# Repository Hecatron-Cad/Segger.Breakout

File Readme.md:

# Segger Breakout

This is a simple kicad design for a breakout board for the JLink Segger.

  * https://www.segger.com/products/debug-probes/j-link/models/j-link-edu/

It also has pads for connecting an ESP32 ProS3, or a Rpi Pico 2040
To clone use
```sh
git clone --recurse-submodules https://github.com/Hecatron-Cad/Segger.Breakout.git
```

## VCC Pins

I've added a jumper for the VCC input to VTref on the segger.
some pages suggest not to connect it when the device is powered over usb, but I think this is incorrect.
Still I added a jumper just in case anyway

  * https://www.visualmicro.com/page/ESP32-Debugging.aspx

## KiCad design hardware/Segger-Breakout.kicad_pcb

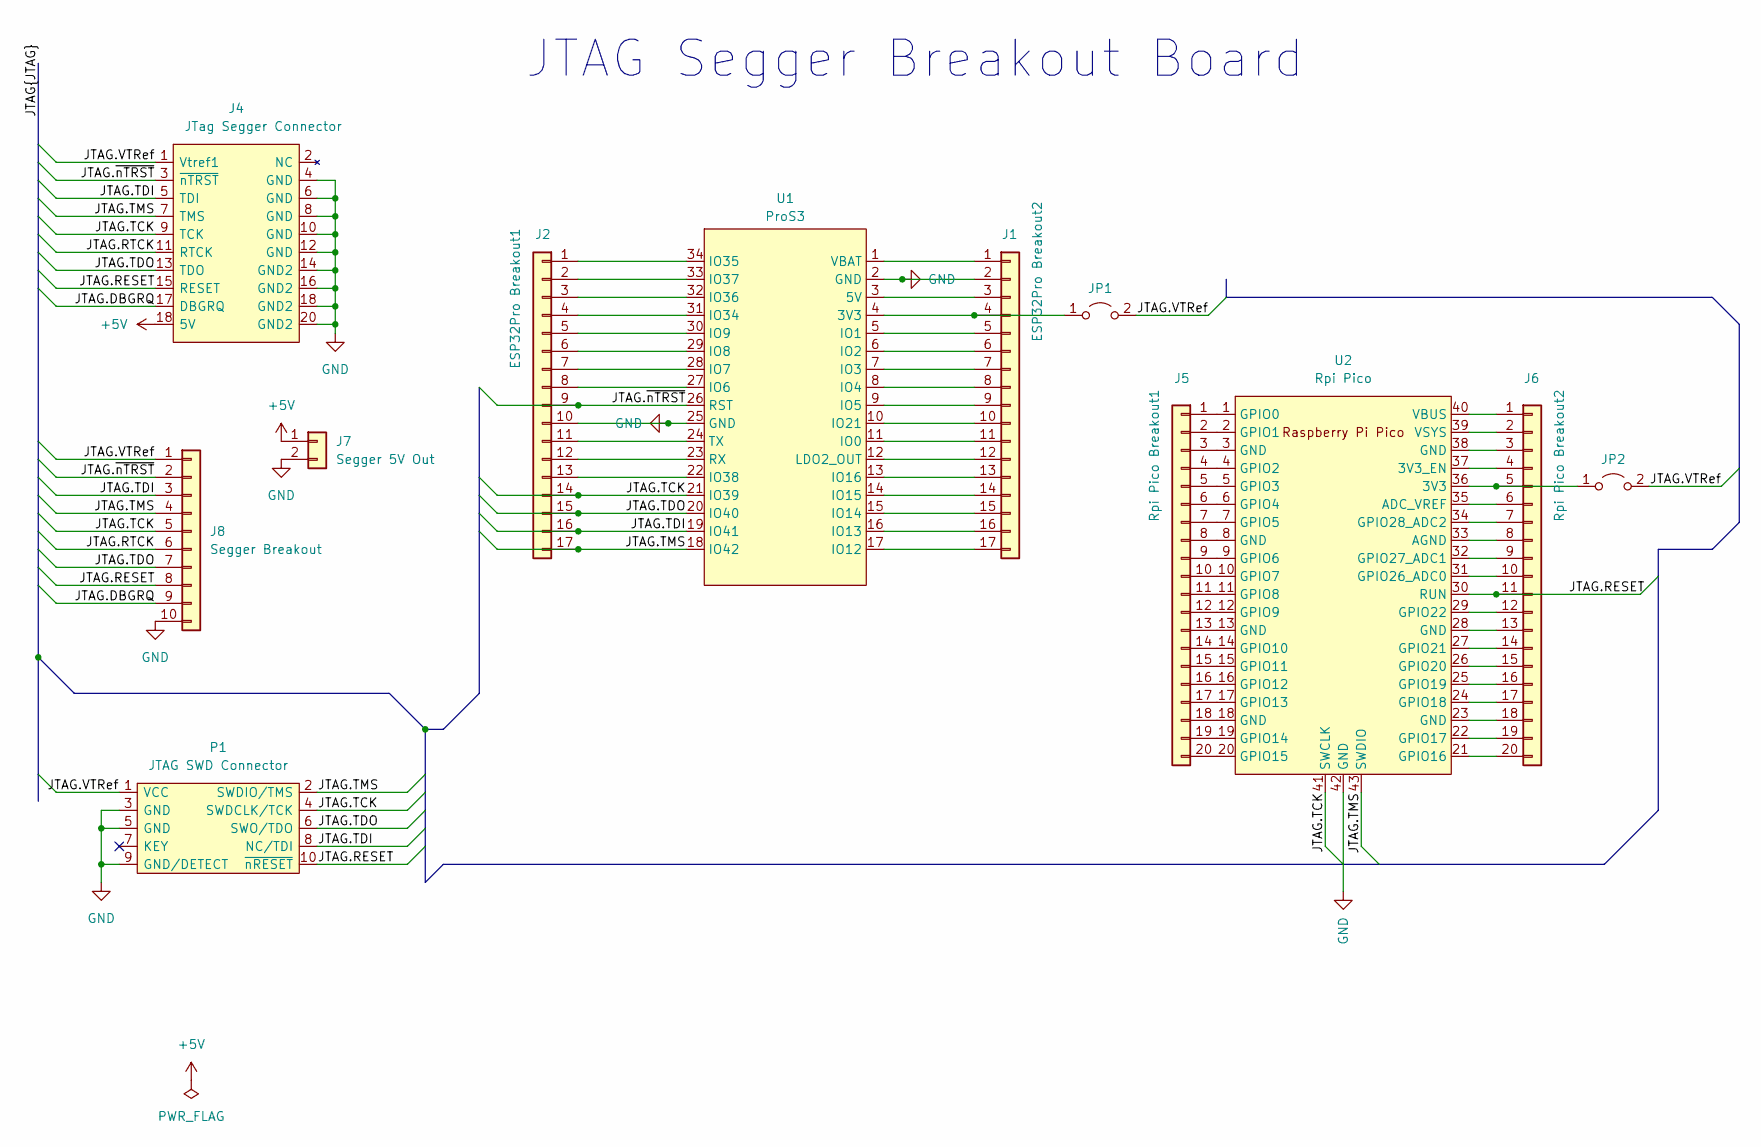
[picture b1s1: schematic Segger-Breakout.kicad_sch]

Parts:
J1: ESP32Pro Breakout2; PinHeader_1x17_P2.54mm_Vertical
J2: ESP32Pro Breakout1; PinHeader_1x17_P2.54mm_Vertical
J4: JTag Segger Connector; IDC-Header_2x10_P2.54mm_Vertical
J5: Rpi Pico Breakout1; PinHeader_1x20_P2.54mm_Vertical
J6: Rpi Pico Breakout2; PinHeader_1x20_P2.54mm_Vertical
J7: Segger 5V Out; PinHeader_1x02_P2.54mm_Vertical
J8: Segger Breakout; PinHeader_1x10_P2.54mm_Vertical
JP1, JP2: VTref Segger Input; PinSocket_1x02_P2.54mm_Vertical
P1: JTAG SWD Connector; ARM_10_PIN
U1: ProS3; ProS3_TH
U2: Rpi Pico; RPi_PicoW_SMD_TH

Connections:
/JTAG.DBGRQ: J4.17 (DBGRQ), J8.9
/JTAG.RESET: J4.15 (RESET), J6.11, J8.8, P1.10 (~nRESET), U2.30 (RUN)
/JTAG.RTCK: J4.11 (RTCK), J8.6
/JTAG.TCK: J2.14, J4.9 (TCK), J8.5, P1.4 (SWDCLK/TCK), U1.21 (IO39), U2.41 (SWCLK)
/JTAG.TDI: J2.16, J4.5 (TDI), J8.3, P1.8 (NC/TDI), U1.19 (IO41)
/JTAG.TDO: J2.15, J4.13 (TDO), J8.7, P1.6 (SWO/TDO), U1.20 (IO40)
/JTAG.TMS: J2.17, J4.7 (TMS), J8.4, P1.2 (SWDIO/TMS), U1.18 (IO42), U2.43 (SWDIO)
/JTAG.VTRef: J4.1 (Vtref1), J8.1, JP1.2 (B), JP2.2 (B), P1.1 (VCC)
/JTAG.~nTRST: J2.9, J4.3 (~nTRST), J8.2, U1.26 (RST)
unnamed: J1.1, U1.1 (VBAT)
unnamed: J1.3, U1.3 (5V)
unnamed: J1.4, JP1.1 (A), U1.4 (3V3)
unnamed: J1.5, U1.5 (IO1)
unnamed: J1.6, U1.6 (IO2)
unnamed: J1.7, U1.7 (IO3)
unnamed: J1.8, U1.8 (IO4)
unnamed: J1.9, U1.9 (IO5)
unnamed: J1.10, U1.10 (IO21)
unnamed: J1.11, U1.11 (IO0)
unnamed: J1.12, U1.12 (LDO2_OUT)
unnamed: J1.13, U1.13 (IO16)
unnamed: J1.14, U1.14 (IO15)
unnamed: J1.15, U1.15 (IO14)
unnamed: J1.16, U1.16 (IO13)
unnamed: J1.17, U1.17 (IO12)
unnamed: J2.1, U1.34 (IO35)
unnamed: J2.2, U1.33 (IO37)
unnamed: J2.3, U1.32 (IO36)
unnamed: J2.4, U1.31 (IO34)
unnamed: J2.5, U1.30 (IO9)
unnamed: J2.6, U1.29 (IO8)
unnamed: J2.7, U1.28 (IO7)
unnamed: J2.8, U1.27 (IO6)
unnamed: J2.11, U1.24 (TX)
unnamed: J2.12, U1.23 (RX)
unnamed: J2.13, U1.22 (IO38)
unnamed: J5.1, U2.1 (GPIO0)
unnamed: J5.2, U2.2 (GPIO1)
unnamed: J5.3, U2.3 (GND)
unnamed: J5.4, U2.4 (GPIO2)
unnamed: J5.5, U2.5 (GPIO3)
unnamed: J5.6, U2.6 (GPIO4)
unnamed: J5.7, U2.7 (GPIO5)
unnamed: J5.8, U2.8 (GND)
unnamed: J5.9, U2.9 (GPIO6)
unnamed: J5.10, U2.10 (GPIO7)
unnamed: J5.11, U2.11 (GPIO8)
unnamed: J5.12, U2.12 (GPIO9)
unnamed: J5.13, U2.13 (GND)
unnamed: J5.14, U2.14 (GPIO10)
unnamed: J5.15, U2.15 (GPIO11)
unnamed: J5.16, U2.16 (GPIO12)
unnamed: J5.17, U2.17 (GPIO13)
unnamed: J5.18, U2.18 (GND)
unnamed: J5.19, U2.19 (GPIO14)
unnamed: J5.20, U2.20 (GPIO15)
unnamed: J6.1, U2.40 (VBUS)
unnamed: J6.2, U2.39 (VSYS)
unnamed: J6.3, U2.38 (GND)
unnamed: J6.4, U2.37 (3V3_EN)
unnamed: J6.5, JP2.1 (A), U2.36 (3V3)
unnamed: J6.6, U2.35 (ADC_VREF)
unnamed: J6.7, U2.34 (GPIO28_ADC2)
unnamed: J6.8, U2.33 (AGND)
unnamed: J6.9, U2.32 (GPIO27_ADC1)
unnamed: J6.10, U2.31 (GPIO26_ADC0)
unnamed: J6.12, U2.29 (GPIO22)
unnamed: J6.13, U2.28 (GND)
unnamed: J6.14, U2.27 (GPIO21)
unnamed: J6.15, U2.26 (GPIO20)
unnamed: J6.16, U2.25 (GPIO19)
unnamed: J6.17, U2.24 (GPIO18)
unnamed: J6.18, U2.23 (GND)
unnamed: J6.19, U2.22 (GPIO17)
unnamed: J6.20, U2.21 (GPIO16)

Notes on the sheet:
JTAG Segger Breakout Board

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
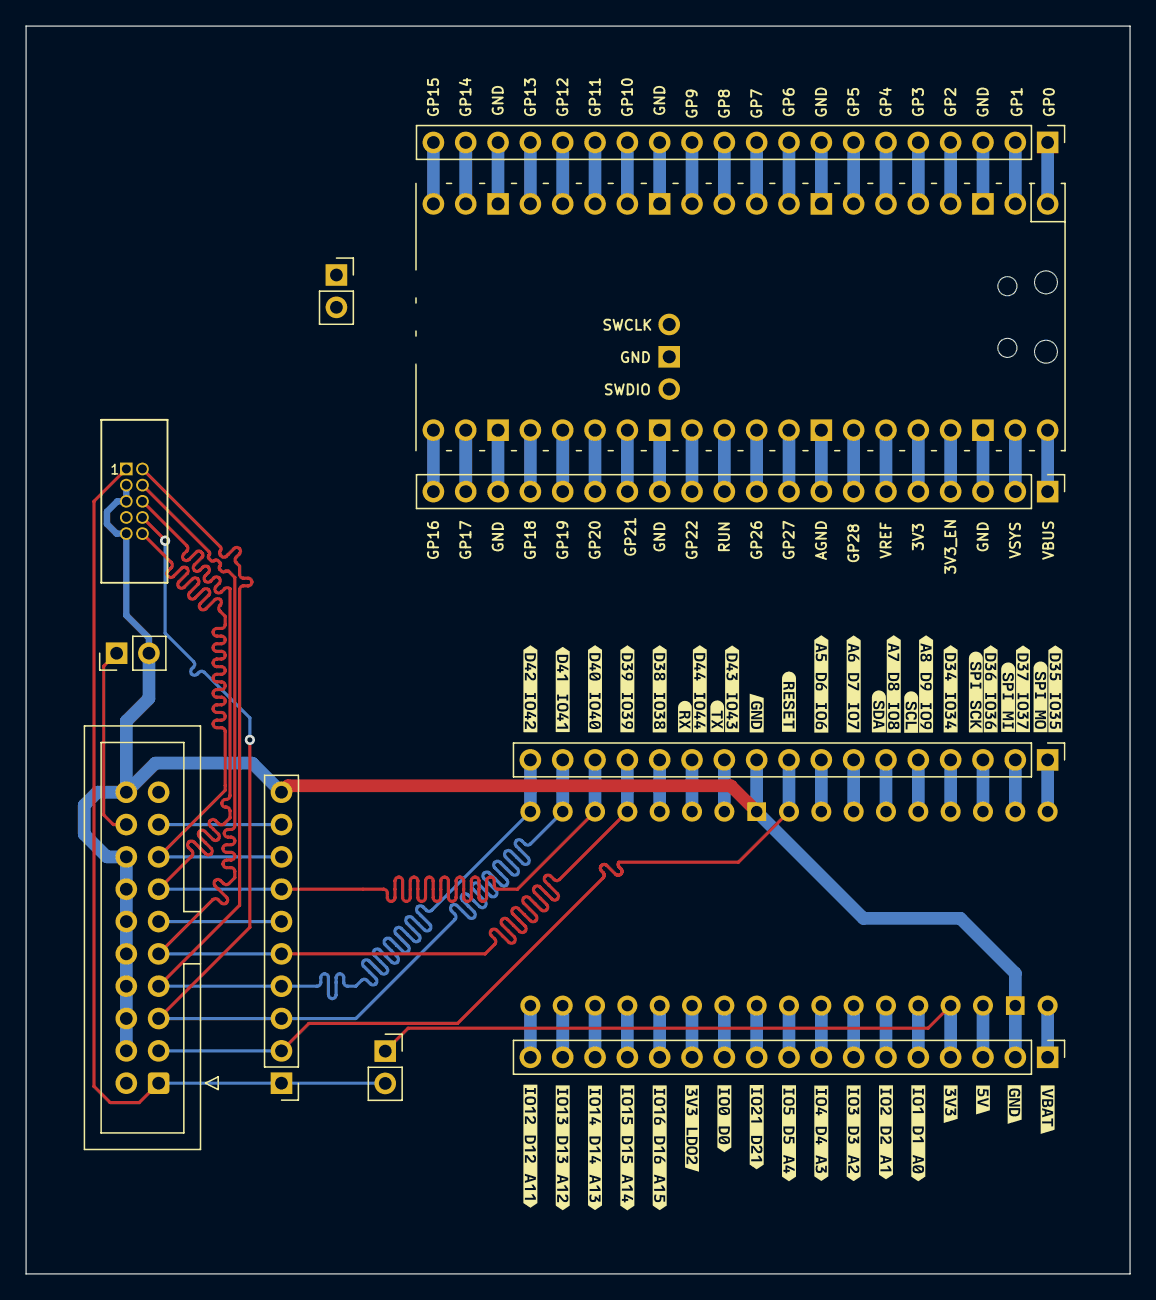
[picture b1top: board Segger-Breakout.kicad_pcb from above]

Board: 2 copper layers, 86.7 x 98.0 mm, 53 parts (0 on the bottom side), 77 nets.

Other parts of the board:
kibuzzard-655FC4B1: G***; kibuzzard-655FC4B1
kibuzzard-655FC6B9: G***; kibuzzard-655FC6B9
kibuzzard-655FC7B2: G***; kibuzzard-655FC7B2
kibuzzard-655FC7D9: G***; kibuzzard-655FC7D9
kibuzzard-655FC9E7: G***; kibuzzard-655FC9E7
kibuzzard-655FC45E: G***; kibuzzard-655FC45E
kibuzzard-655FC52C: G***; kibuzzard-655FC52C
kibuzzard-655FC56D: G***; kibuzzard-655FC56D
kibuzzard-655FC60E: G***; kibuzzard-655FC60E
kibuzzard-655FC61C: G***; kibuzzard-655FC61C
kibuzzard-655FC469: G***; kibuzzard-655FC469
kibuzzard-655FC471: G***; kibuzzard-655FC471
kibuzzard-655FC478: G***; kibuzzard-655FC478
kibuzzard-655FC607: G***; kibuzzard-655FC607
kibuzzard-655FC616: G***; kibuzzard-655FC616
kibuzzard-655FC635: G***; kibuzzard-655FC635
kibuzzard-655FC710: G***; kibuzzard-655FC710
kibuzzard-655FC738: G***; kibuzzard-655FC738
kibuzzard-655FC940: G***; kibuzzard-655FC940
kibuzzard-655FC954: G***; kibuzzard-655FC954
kibuzzard-655FCA04: G***; kibuzzard-655FCA04
kibuzzard-655FCA7F: G***; kibuzzard-655FCA7F
kibuzzard-655FCA38: G***; kibuzzard-655FCA38
kibuzzard-655FCA61: G***; kibuzzard-655FCA61
kibuzzard-655FCAAA: G***; kibuzzard-655FCAAA
kibuzzard-655FCAFA: G***; kibuzzard-655FCAFA
kibuzzard-655FCB2A: G***; kibuzzard-655FCB2A
kibuzzard-655FCBAC: G***; kibuzzard-655FCBAC
kibuzzard-655FCC1E: G***; kibuzzard-655FCC1E
kibuzzard-655FCC6B: G***; kibuzzard-655FCC6B
kibuzzard-655FCC8E: G***; kibuzzard-655FCC8E
kibuzzard-655FCC41: G***; kibuzzard-655FCC41
kibuzzard-655FCCA3: G***; kibuzzard-655FCCA3
kibuzzard-655FCCAF: G***; kibuzzard-655FCCAF
kibuzzard-655FCD75: G***; kibuzzard-655FCD75
kibuzzard-655FCDA8: G***; kibuzzard-655FCDA8
kibuzzard-655FCDCF: G***; kibuzzard-655FCDCF
kibuzzard-655FCDDC: G***; kibuzzard-655FCDDC
kibuzzard-655FCE5C: G***; kibuzzard-655FCE5C
kibuzzard-655FCE13: G***; kibuzzard-655FCE13
kibuzzard-655FCE50: G***; kibuzzard-655FCE50

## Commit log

2023-11-20 added submodule
2023-11-21 schematic updates
2023-11-21 pcb updates
